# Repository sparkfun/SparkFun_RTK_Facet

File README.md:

SparkFun RTK Facet
========================================

<table class="table table-hover table-striped table-bordered">
  <tr align="center">
   <td></td>
   <td></td>
  <tr align="center">
    <td><a href="https://www.sparkfun.com/products/20000">SparkFun RTK Facet L-Band (GPS-20000)</a></td>
    <td><a href="https://www.sparkfun.com/products/19029">SparkFun RTK Facet (GPS-19029)</a></td>
  </tr>
</table>

The SparkFun RTK Facet and RTK Facet L-Band are your one stop shop for high precision geolocation and surveying needs. For basic users, it’s incredibly easy to get up and running and for advanced users, the RTK Facet is a flexible and powerful tool. With just a few minutes of setup, the RTK Facet is one of the fastest ways to take centimeter grade measurements. By connecting your phone to the RTK Facet over Bluetooth, your phone can act as the radio link to provide correction data as well as receive the NMEA output from the device. This is exactly how $10,000 surveying devices have been operating for the past decade - we just made it easier, smaller, and a lot cheaper. 

The RTK Facet L-Band utilizes corrections from u-blox's PointPerfect service broadcast from a geosynchronous Inmarsat satellite. The only setup required is a WiFi SSID and password. Once entered, the device will provision itself and periodically (once a month) update the decryption keys necessary to use the PointPerfect service. The price of the RTK Facet L-Band includes a 12-month subscription. Additional years of service can be purchased.

Under the hood of the SparkFun RTK Facet is an ESP32 WROOM connected to a ZED-F9P as well as some peripheral hardware (OLED, LiPo fuel gauge, microSD, etc). Additionally, housed under the dome of the RTK Facet is a surveyor grade L1/L2 antenna. It is the same element found within our GNSS Multi-Band L1/L2 Surveying Antenna.

Under the hood of the SparkFun RTK Facet L-Band is an ESP32 WROOM connected to a ZED-F9P GNSS receiver, a NEO-D9S L-Band receiver (for corrections), and a variety of peripheral hardware (LiPo fuel gauge, microSD, etc). Additionally, housed under the dome of the RTK Facet L-Band is a surveyor grade L1/L2/L-Band antenna. This antenna is a unique combination of elements designed to receive the GNSS signals (L1/L2) alongside the 1.55GHz PointPerfect corrections. The built-in antenna has an ARP of 69mm from the base to the measuring point of the L1 antenna and an ARP of 68mm to the measuring point of the L2 antenna. The RTK Facet L-Band is programmed in Arduino and can be tailored by you to fit whatever your needs may be.

Repository Contents
-------------------

* **/Documents** - Datasheets and additional product information
* **/Hardware** - Eagle PCB files
* **/Labels** - Display overlay and info stickers
* **/Mechanical** - Drawings use to created injection molding tooling

Documentation
--------------

* **[RTK Product Manual](https://docs.sparkfun.com/SparkFun_RTK_Firmware/)** - A detailed guide describing all the various software features of the RTK product line. Essentially it is a manual for the firmware used by the RTK Facet.
* **[RTK Facet L-Band Hookup Guide](https://learn.sparkfun.com/tutorials/sparkfun-rtk-facet-l-band-hookup-guide)** - Hookup guide for the SparkFun RTK Facet L-Band.
* **[RTK Facet Hookup Guide](https://learn.sparkfun.com/tutorials/sparkfun-rtk-facet-hookup-guide)** - Hookup guide for the SparkFun RTK Facet.

License Information
-------------------

This product is _**open source**_! 

Please review the LICENSE.md file for license information. 

If you have any questions or concerns on licensing, please contact technical support on our [SparkFun forums](https://forum.sparkfun.com/viewforum.php?f=152).

Distributed as-is; no warranty is given.

- Your friends at SparkFun.

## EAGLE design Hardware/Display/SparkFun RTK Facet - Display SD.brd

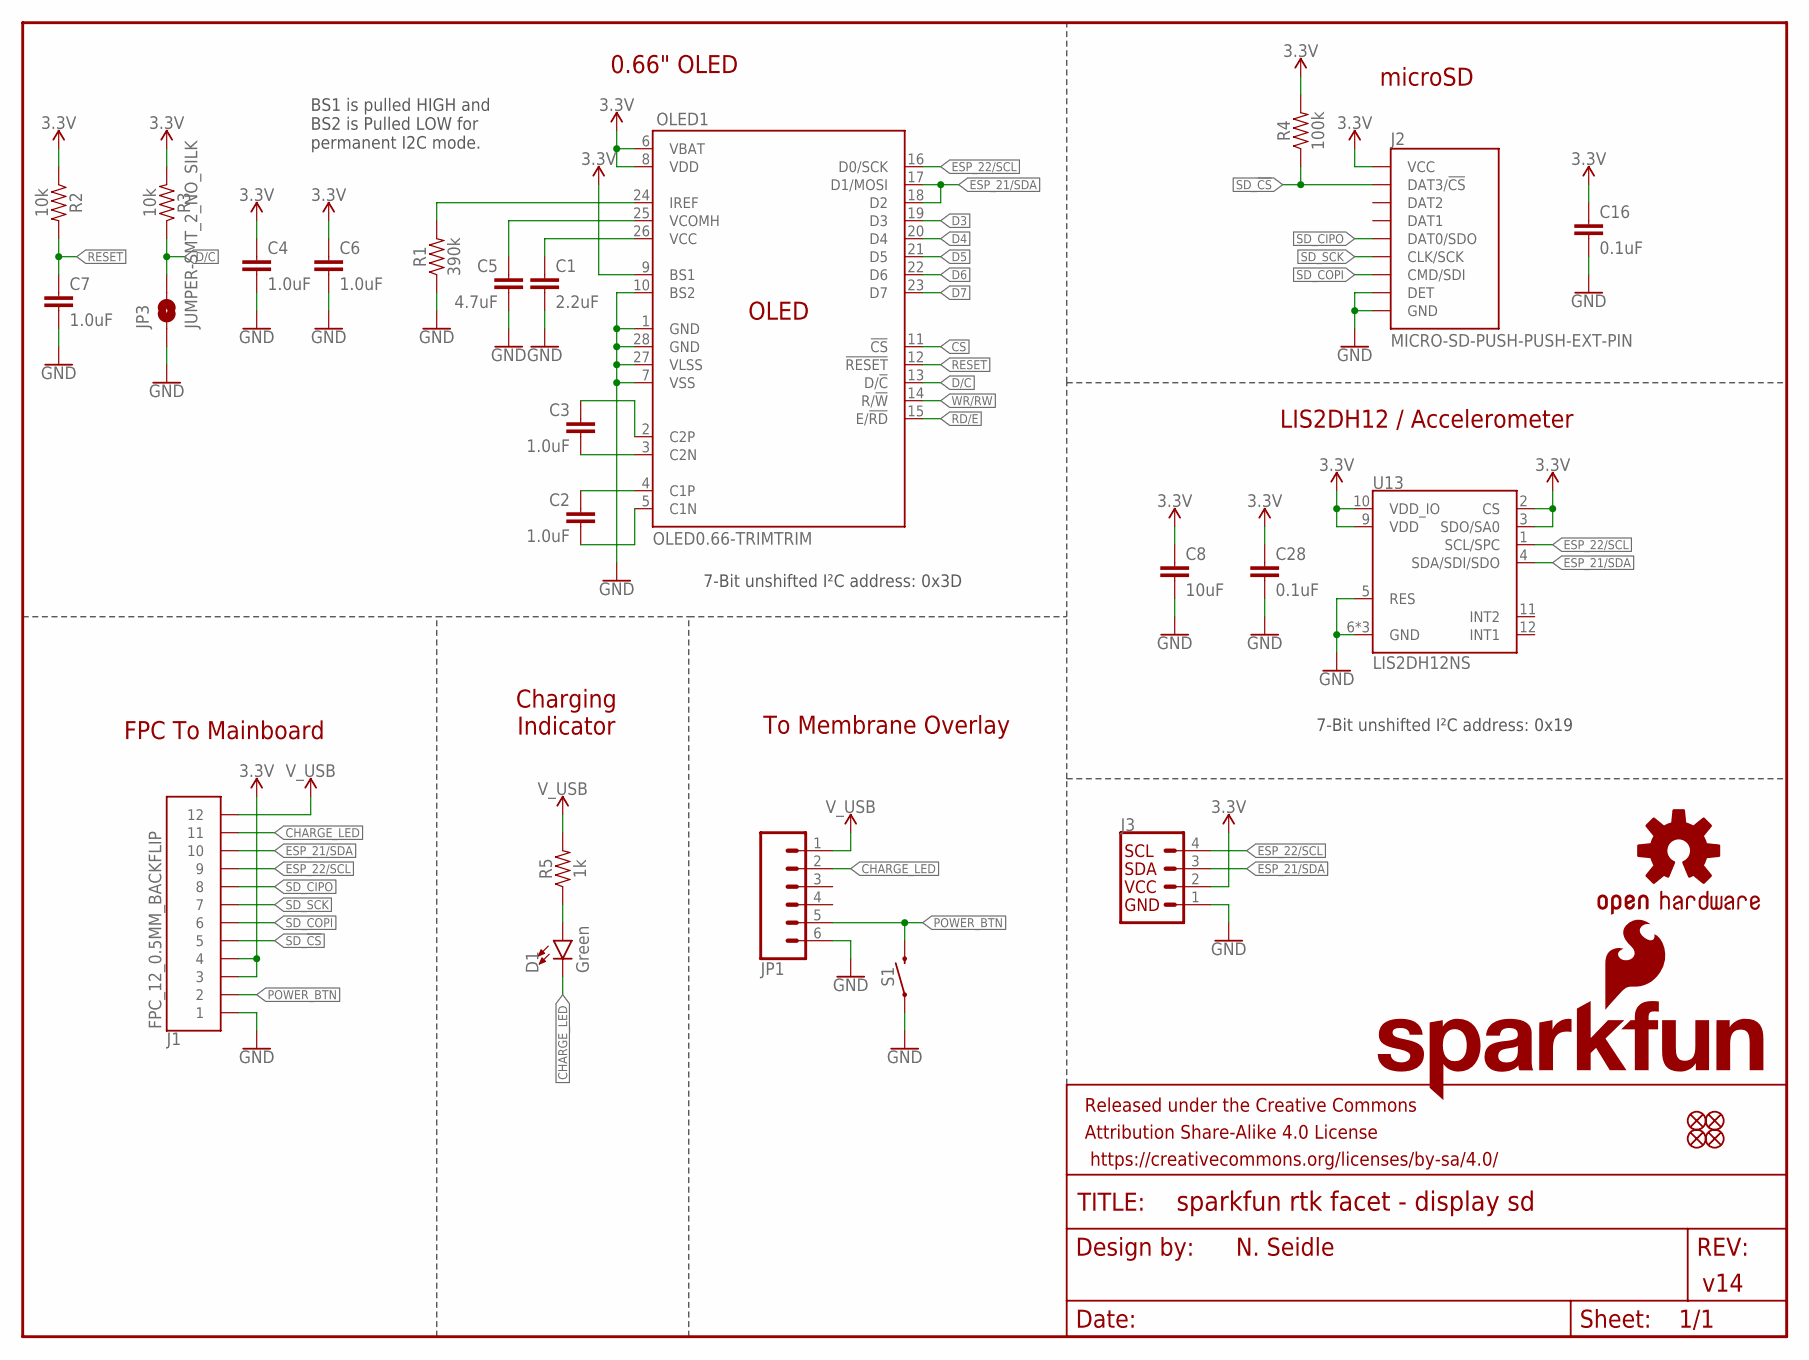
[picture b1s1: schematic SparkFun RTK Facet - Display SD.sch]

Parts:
C1: 2.2uF; 0805
C2, C3: 1.0uF; 0805
C4, C6, C7: 1.0uF; 0603
C5: 4.7uF; 1206
C8: 10uF; 0603
C16, C28: 0.1uF; 0603
D1: Green; LED-1206-BOTTOM
FID1, FID2, FID3, FID4: FIDUCIAL1X2; FIDUCIAL-1X2
FRAME1: FRAME-LETTER; CREATIVE_COMMONS
J1: FPC_12_0.5MM_BACKFLIP; FPC_12_DOUBLESIDED_BACKFLIP
J2: MICRO-SD-PUSH-PUSH-EXT-PIN; MICROSD-EXTERNALPIN
J3: I2C_STANDARD_NO_SILK; 1X04_NO_SILK
JP1: CONN_061MM-LIF; FPC_6_1MM-LIF
JP3: JUMPER-SMT_2_NO_SILK; SMT-JUMPER_2_NO_SILK
LOGO3: OSHW-LOGOMINI; OSHW-LOGO-MINI
LOGO5: SFE_LOGO_NAME_FLAME8_MM; SFE_LOGO_NAME_FLAME_8MM
OLED1: OLED0.66-TRIMTRIM; OLED-0.66-64X48-TRIM
R1: 390k; 0603
R2, R3: 10k; 0603
R4: 100k; 0603
R5: 1k; 0603
S1: MOMENTARY-SWITCH-SPST-SMD-5.2MM-TALL; TACTILE_SWITCH_SMD_5.2MM
U13: LIS2DH12NS; LGA-12-LISDH12-NOSILK

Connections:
3.3V: C4.1, C6.1, C8.1, C16.1, C28.1, J1.3, J1.4, J2.4 (VCC), J3.2, OLED1.6 (VBAT), OLED1.8 (VDD), OLED1.9 (BS1), R2.1, R3.2, R4.2, U13.2 (CS), U13.3 (SDO/SA0), U13.9 (VDD), U13.10 (VDD_IO)
C1P: C2.1, OLED1.4 (C1P)
C2N: C3.2, OLED1.3 (C2N)
CHARGE_LED: D1.C, J1.11, JP1.2
CS: OLED1.11 (!CS!)
D3: OLED1.19 (D3)
D4: OLED1.20 (D4)
D5: OLED1.21 (D5)
D6: OLED1.22 (D6)
D7: OLED1.23 (D7)
D/C: JP3.2, OLED1.13 (D/!C!), R3.1
ESP_21/SDA: J1.10, J3.3, OLED1.17 (D1/MOSI), OLED1.18 (D2), U13.4 (SDA/SDI/SDO)
ESP_22/SCL: J1.9, J3.4, OLED1.16 (D0/SCK), U13.1 (SCL/SPC)
GND: C1.2, C4.2, C5.2, C6.2, C7.2, C8.2, C16.2, C28.2, J1.1, J2.6 (GND), J2.9 (DET), J2.10 (GND), J2.11 (GND), J2.12 (GND), J2.13 (GND), J3.1, JP1.6, JP3.1, OLED1.1 (GND), OLED1.7 (VSS), OLED1.10 (BS2), OLED1.27 (VLSS), OLED1.28 (GND), R1.1, S1.1, U13.5 (RES), U13.6 (GND), U13.7 (GND), U13.8 (GND)
IREF: OLED1.24 (IREF), R1.2
unnamed: C3.1, OLED1.2 (C2P)
unnamed: C2.2, OLED1.5 (C1N)
unnamed: D1.A, R5.1
POWER_BTN: J1.2, JP1.5, S1.3 (2)
RD/E: OLED1.15 (E/!RD!)
RESET: C7.1, OLED1.12 (!RESET!), R2.2
SD_!CS!: J1.5, J2.2 (DAT3/!CS!), R4.1
SD_CIPO: J1.8, J2.7 (DAT0/SDO)
SD_COPI: J1.6, J2.3 (CMD/SDI)
SD_SCK: J1.7, J2.5 (CLK/SCK)
VCC: C1.1, OLED1.26 (VCC)
VCOMH: C5.1, OLED1.25 (VCOMH)
V_USB: J1.12, JP1.1, R5.2
WR/RW: OLED1.14 (R/!W!)

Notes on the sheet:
v14
FPC To Mainboard
BS1 is pulled HIGH and BS2 is Pulled LOW for permanent I2C mode.
microSD
7-Bit unshifted I²C address: 0x19
LIS2DH12 / Accelerometer
To Membrane Overlay
0.66" OLED
Charging Indicator
N. Seidle
7-Bit unshifted I²C address: 0x3D

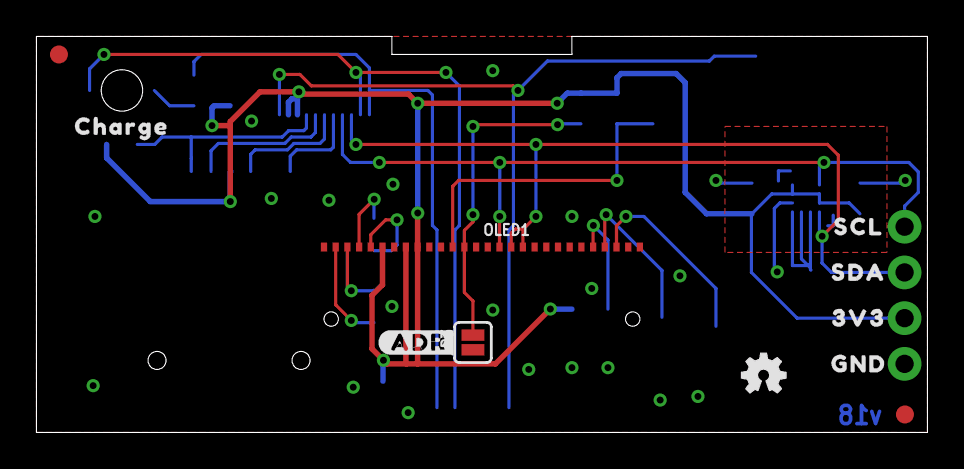
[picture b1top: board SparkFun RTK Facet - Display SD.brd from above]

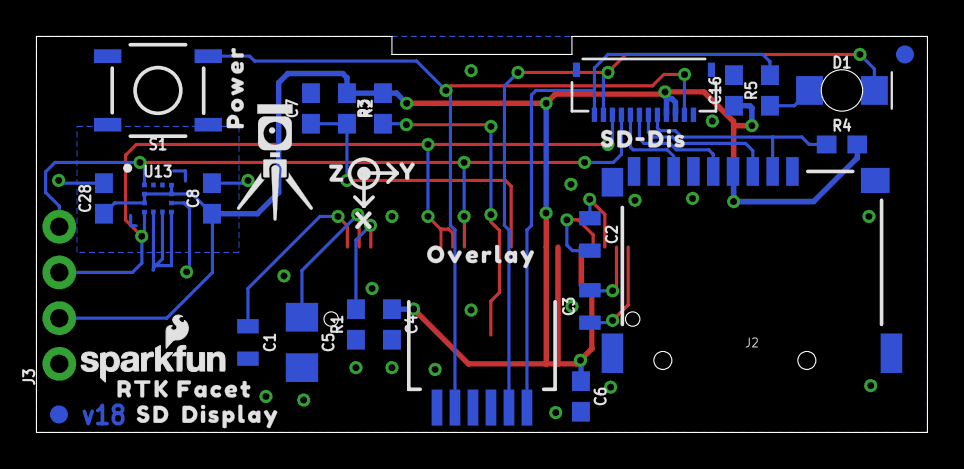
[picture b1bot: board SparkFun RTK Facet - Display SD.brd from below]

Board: 2 copper layers, 49.5 x 22.0 mm, 48 parts (37 on the bottom side), 21 nets.

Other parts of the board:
U$1: SD#DIS0
U$2: OVERLAY0
U$3: DISPLAY0
U$4: SD1
U$5: RTK5#SVG0
U$6: SPECIAL_INSTRUCTIONS-ORDERING; ORDERING_INSTRUCTIONS
U$7: #ADR#0
U$8: CHARGE0
U$9: POWER0
U$10: X0
U$11: Y1
U$12: Z2
U$13: RTK_FACET0
U$14: 3V33
U$15: GND2
U$16: SCL0
U$17: SDA1

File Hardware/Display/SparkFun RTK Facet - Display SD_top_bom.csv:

Comment,Designator,Footprint,LCSC Part #
OLED0.66-TRIMTRIM,OLED1,OLED-0.66-64X48-TRIM,C88334 
0.1uF,C16 C28,603,C1590 
1.0uF,C2 C3,805,C15849 
1.0uF,C4 C6 C7,603,C1592 
1k,R5,603,C22548 
2.2uF,C1,805,C19110 
4.7uF,C5,1206,C51205 
10k,R2 R3,603,C98220 
10uF,C8,603,C19702 
100k,R4,603,C14675 
390k,R1,603,C863775 
FPC_12_0.5MM_BACKFLIP,J1,FPC_12_DOUBLESIDED_BACKFLIP,C5213751 
Green,D1,LED-1206-BOTTOM,C125106 
MICRO-SD-PUSH-PUSH-EXT-PIN,J2,MICROSD-EXTERNALPIN,C720505 
MOMENTARY-SWITCH-SPST-SMD-5.2MM-TALL,S1,TACTILE_SWITCH_SMD_5.2MM,C318887 
6P_1MM-LIF Connector,JP1,6P_1MM-LIF Connector,C2915488

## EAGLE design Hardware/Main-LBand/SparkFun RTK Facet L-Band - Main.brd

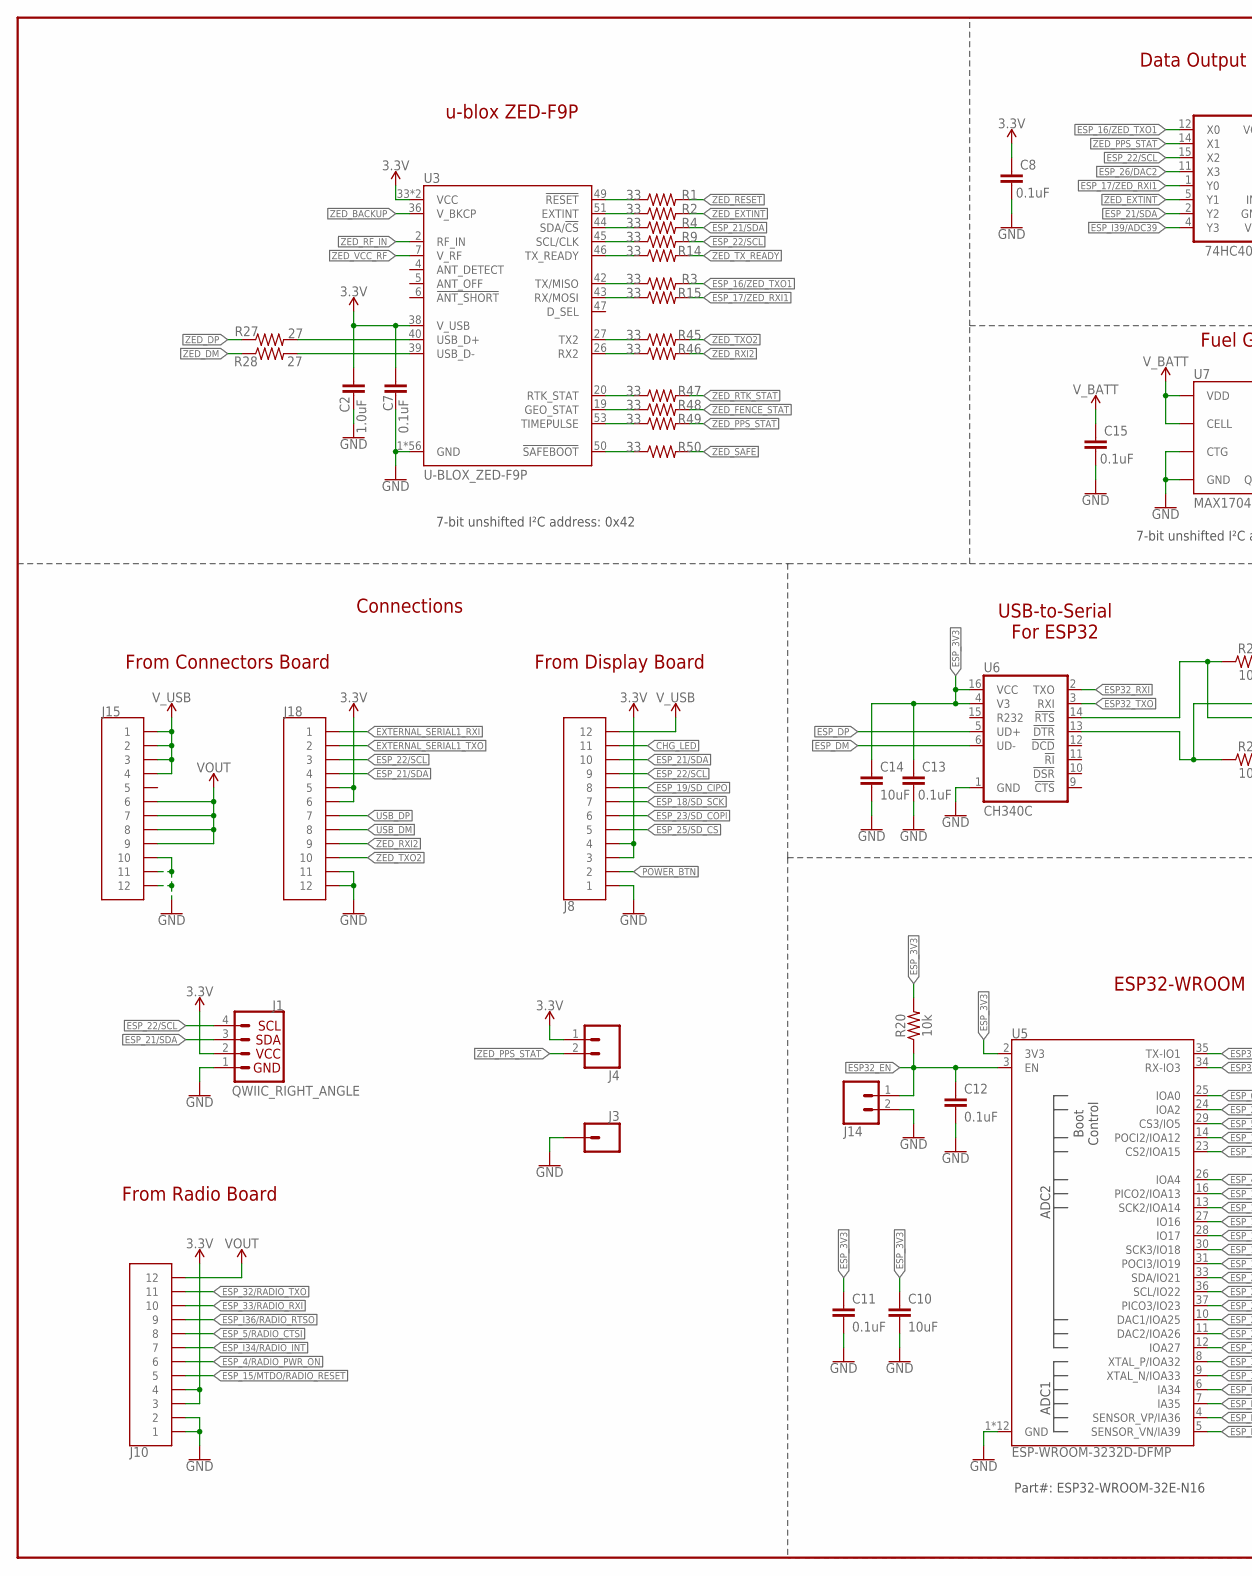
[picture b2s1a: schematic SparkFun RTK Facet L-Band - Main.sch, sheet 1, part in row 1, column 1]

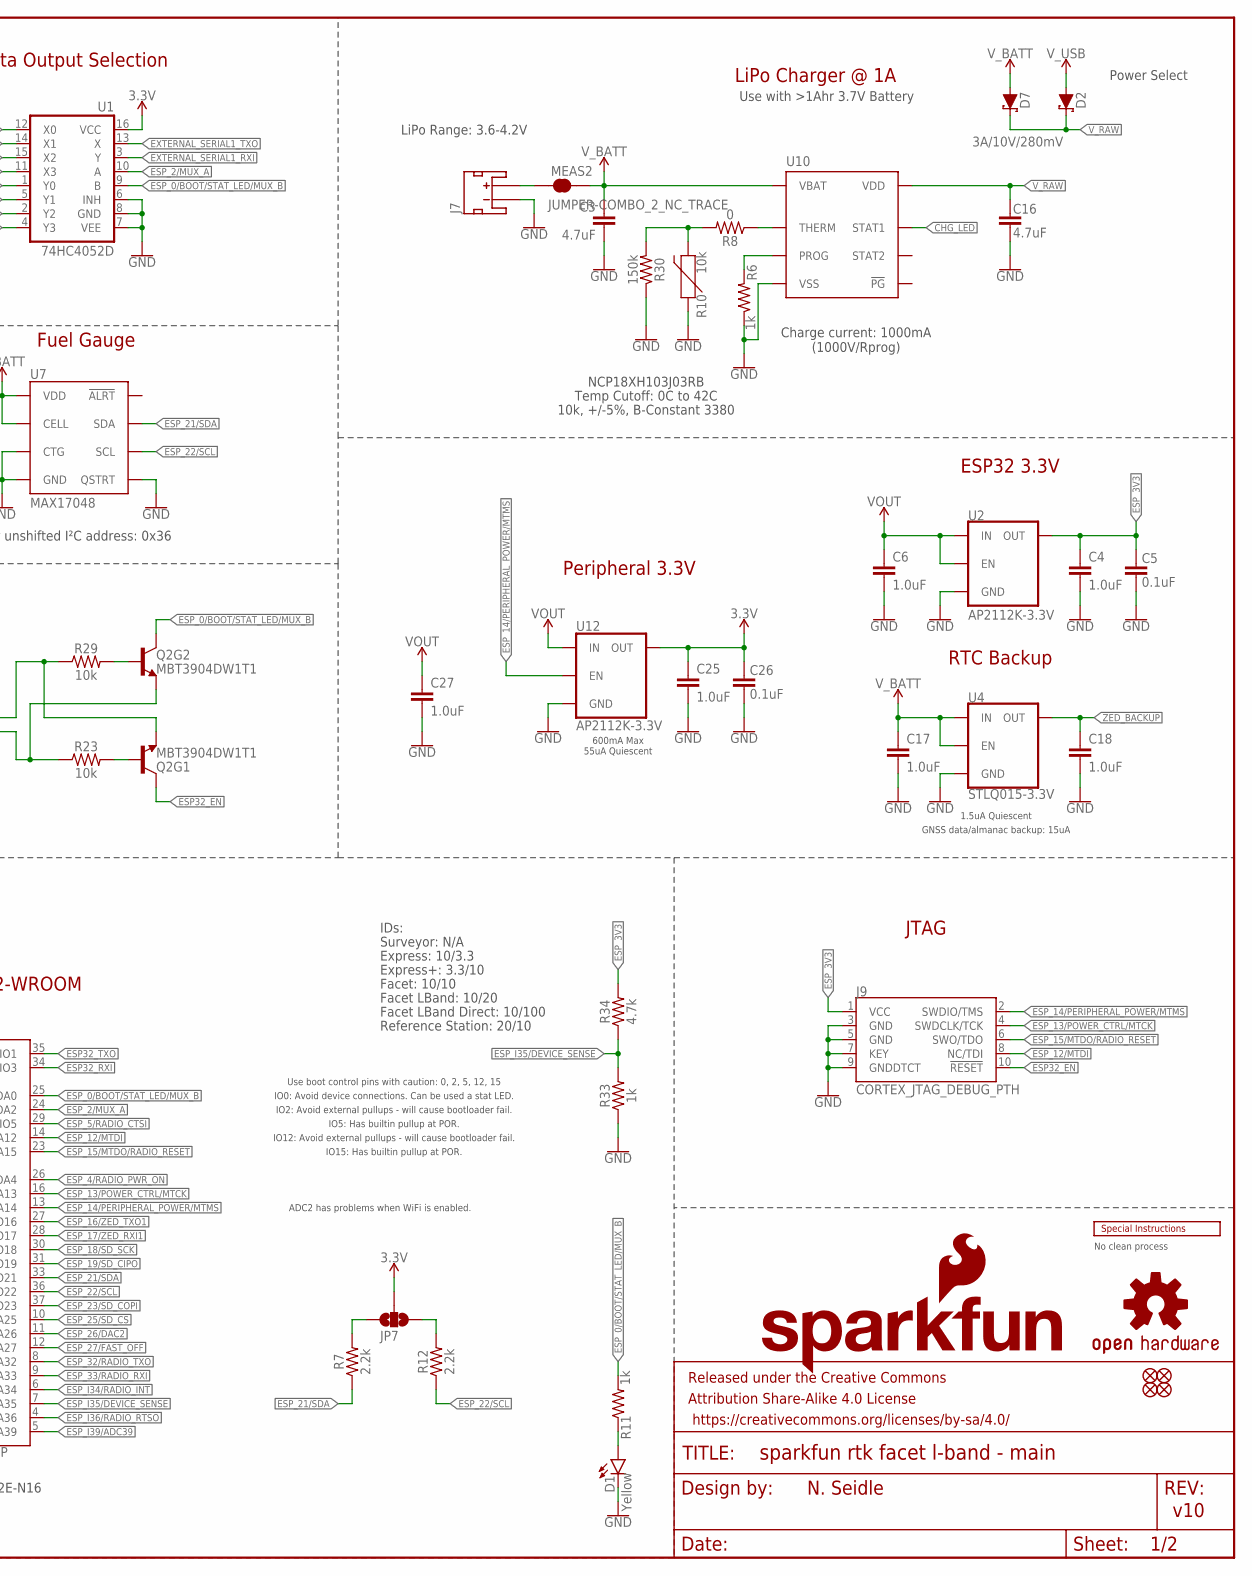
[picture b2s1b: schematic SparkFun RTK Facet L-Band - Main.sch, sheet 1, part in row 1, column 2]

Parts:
C2, C4, C6, C17, C18, C25, C27: 1.0uF; 0603
C3, C16: 4.7uF; 0603
C5, C7, C8, C11, C12, C13, C15, C26: 0.1uF; 0603
C10, C14: 10uF; 0603
D1: Yellow; LED-0603
D2, D7: 3A/10V/280mV; SOD-323
FRAME2: FRAME-LEDGER; CREATIVE_COMMONS
J1: QWIIC_RIGHT_ANGLE; JST04_1MM_RA
J3: CONN_01PTH_NO_SILK_YES_STOP; 1X01_NO_SILK
J4, J14: CONN_021X02_NO_SILK; 1X02_NO_SILK
J7: JST_2MM_MALE; JST-2-SMD
J8, J10, J15, J18: FPC_12_0.5MM_BACKFLIP; FPC_12_DOUBLESIDED_BACKFLIP
J9: CORTEX_JTAG_DEBUG_PTH; 2X5-PTH-1.27MM
JP7: JUMPER-SMT_3_NO_SILK; SMT-JUMPER_3_NO_SILK
JP21, JP61, JP71, JP81: FIDUCIALUFIDUCIAL; FIDUCIAL-MICRO
LOGO1: OSHW-LOGOMINI; OSHW-LOGO-MINI
LOGO2: SFE_LOGO_NAME_FLAME.1_INCH; SFE_LOGO_NAME_FLAME_.1
MEAS2: JUMPER-COMBO_2_NC_TRACE; COMBO-JUMPER_2_NC_TRACE
Q2: MBT3904DW1T1; SC70-6
R1, R2, R3, R4, R9, R14, R15, R45, R46, R47, R48, R49, R50: 33; 0603
R6, R11, R33: 1k; 0603
R7, R12: 2.2k; 0603
R8: 0; 0603
R10, R20, R23, R29: 10k; 0603
R27, R28: 27; 0603
R30: 150k; 0603
R34: 4.7k; 0603
U1: 74HC4052D; SO16
U2, U12: AP2112K-3.3V; SOT23-5
U3: U-BLOX_ZED-F9P; ZED-F9P
U4: STLQ015-3.3V; SOT23-5
U5: ESP-WROOM-3232D-DFMP; ESP-WROOM-32D-DFM_PASTE
U6: CH340C; SO016
U7: MAX17048; DFN-8
U10: MCP73833MSOP; MSOP10
U$2: SPECIAL_INSTRUCTIONS-ORDERING; ORDERING_INSTRUCTIONS

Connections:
3.3V: C2.1, C7.2, C8.1, C25.1, C26.2, J1.2, J4.1, J8.3, J8.4, J10.3, J10.4, J18.5, J18.6, JP7.2, U1.16 (VCC), U3.33 (VCC), U3.34 (VCC), U3.38 (V_USB), U12.5 (OUT); also elsewhere on the board
CHG_LED: J8.11, U10.3 (STAT1)
CHG_THERM1: R8.2, R10.2, R30.2
ESP32_!DTR: Q2.1 (E), R23.1, U6.13 (!DTR)
ESP32_!RTS: Q2.4 (E), R29.1, U6.14 (!RTS)
ESP32_EN: C12.1, J9.10 (!RESET), J14.1, Q2.3 (C), R20.1, U5.3 (EN)
ESP32_RXI: U5.34 (RX-IO3), U6.2 (TXO)
ESP32_TXO: U5.35 (TX-IO1), U6.3 (RXI)
ESP_0/BOOT/STAT_LED/MUX_B: Q2.6 (C), R11.2, U1.9 (B), U5.25 (IOA0)
ESP_2/MUX_A: U1.10 (A), U5.24 (IOA2)
ESP_3V3: C4.1, C5.2, C10.1, C11.1, C13.1, C14.1, J9.1 (VCC), R20.2, R34.2, U2.5 (OUT), U5.2 (3V3), U6.4 (V3), U6.16 (VCC); also elsewhere on the board
ESP_4/RADIO_PWR_ON: J10.6, U5.26 (IOA4)
ESP_5/RADIO_CTSI: J10.8, U5.29 (CS3/IO5)
ESP_12/MTDI: J9.8 (NC/TDI), U5.14 (POCI2/IOA12)
ESP_13/POWER_CTRL/MTCK: J9.4 (SWDCLK/TCK), U5.16 (PICO2/IOA13); also elsewhere on the board
ESP_14/PERIPHERAL_POWER/MTMS: J9.2 (SWDIO/TMS), U5.13 (SCK2/IOA14), U12.3 (EN)
ESP_15/MTDO/RADIO_!RESET!: J9.6 (SWO/TDO), J10.5, U5.23 (CS2/IOA15)
ESP_16/ZED_TXO1: R3.2, U1.12 (X0), U5.27 (IO16)
ESP_17/ZED_RXI1: R15.2, U1.1 (Y0), U5.28 (IO17)
ESP_18/SD_SCK: J8.7, U5.30 (SCK3/IO18)
ESP_19/SD_CIPO: J8.8, U5.31 (POCI3/IO19)
ESP_21/SDA: J1.3, J8.10, J18.4, R4.2, R7.1, U1.2 (Y2), U5.33 (SDA/IO21), U7.8 (SDA); also elsewhere on the board
ESP_22/SCL: J1.4, J8.9, J18.3, R9.2, R12.1, U1.15 (X2), U5.36 (SCL/IO22), U7.7 (SCL); also elsewhere on the board
ESP_23/SD_COPI: J8.6, U5.37 (PICO3/IO23)
ESP_25/SD_!CS!: J8.5, U5.10 (DAC1/IOA25)
ESP_26/DAC2: U1.11 (X3), U5.11 (DAC2/IOA26)
ESP_27/FAST_OFF: U5.12 (IOA27); also elsewhere on the board
ESP_32/RADIO_TXO: J10.11, U5.8 (XTAL_P/IOA32)
ESP_33/RADIO_RXI: J10.10, U5.9 (XTAL_N/IOA33)
ESP_DM: U6.6 (UD-); also elsewhere on the board
ESP_DP: U6.5 (UD+); also elsewhere on the board
ESP_I34/RADIO_INT: J10.7, U5.6 (IA34)
ESP_I35/DEVICE_SENSE: R33.2, R34.1, U5.7 (IA35)
ESP_I36/RADIO_RTSO: J10.9, U5.4 (SENSOR_VP/IA36)
ESP_I39/ADC39: U1.4 (Y3), U5.5 (SENSOR_VN/IA39)
EXTERNAL_SERIAL1_RXI: J18.1, U1.3 (Y)
EXTERNAL_SERIAL1_TXO: J18.2, U1.13 (X)
FENCE_LV: R48.1, U3.19 (GEO_STAT)
GND: C2.2, C3.2, C4.2, C5.1, C6.2, C7.1, C8.2, C10.2, C11.2, C12.2, C13.2, C14.2, C15.2, C16.2, C17.2, C18.2, C25.2, C26.1, C27.2, D1.C, J1.1, J3.1, J7.1 (-), J8.1, J9.3 (GND), J9.5 (GND), J9.7 (KEY), J9.9 (GNDDTCT), J10.1, J10.2, J14.2, J15.10, J15.11, J15.12, J18.11, J18.12, R6.1, R10.1, R30.1, R33.1, U1.6 (INH), U1.7 (VEE), U1.8 (GND), U2.2 (GND), U3.1 (GND), U3.3 (GND), U3.12 (GND), U3.14 (GND), U3.32 (GND), U3.37 (GND), U3.41 (GND), U3.48 (GND), U3.55 (GND), U3.56 (GND), U3.57 (GND), U3.58 (GND), U3.59 (GND), U3.60 (GND), U3.61 (GND), U3.62 (GND), U3.63 (GND), U3.64 (GND), U3.65 (GND), U3.66 (GND), U3.67 (GND), U3.68 (GND), U3.69 (GND), U3.70 (GND), U3.71 (GND), U3.72 (GND), U3.73 (GND), U3.74 (GND), U3.75 (GND), U3.76 (GND), U3.77 (GND), U3.78 (GND), U3.79 (GND), U3.80 (GND), U3.81 (GND), U3.82 (GND), U3.83 (GND), U3.84 (GND), U3.85 (GND), U3.86 (GND), U3.87 (GND), U3.88 (GND), U3.89 (GND), U3.90 (GND), U3.91 (GND), U3.92 (GND), U3.93 (GND), U3.94 (GND), U3.95 (GND), U3.96 (GND), U3.97 (GND), U3.98 (GND), U3.99 (GND), U3.100 (GND), U3.101 (GND), U3.102 (GND), U4.2 (GND), U5.1 (GND), U5.15 (GND), U5.38 (GND), U5.GND, U5.GNDT1 (GND), U5.GNDT2 (GND), U5.GNDT3 (GND), U5.GNDT4 (GND), U5.GNDT5 (GND), U5.GNDT6 (GND), U5.GNDT7 (GND), U5.GNDT8 (GND), U6.1 (GND), U7.1 (CTG), U7.4 (GND), U7.6 (QSTRT), U7.9 (GND), U10.5 (VSS), U12.2 (GND); also elsewhere on the board
LIPO_RAW: J7.2 (+), MEAS2.1, MEAS2.3 (1)
unnamed: R8.1, U10.8 (THERM)
unnamed: D1.A, R11.1
unnamed: JP7.3, R7.2
unnamed: JP7.1, R12.2
unnamed: R2.1, U3.51 (EXTINT)
unnamed: R27.2, U3.40 (USB_D+)
unnamed: R28.2, U3.39 (USB_D-)
unnamed: R1.1, U3.49 (!RESET!)
unnamed: R50.1, U3.50 (!SAFEBOOT!)
unnamed: R14.1, U3.46 (TX_READY)
unnamed: Q2.5 (B), R23.2
unnamed: Q2.2 (B), R29.2
POWER_BTN: J8.2; also elsewhere on the board
PPS: R49.1, U3.53 (TIMEPULSE)
PROG1: R6.2, U10.6 (PROG)
RTK_LV: R47.1, U3.20 (RTK_STAT)
RX2_LV: R46.1, U3.26 (RX2)
RXLV: R15.1, U3.43 (RX/MOSI)
SCL_LV: R9.1, U3.45 (SCL/CLK)
SDA_LV: R4.1, U3.44 (SDA/!CS!)
TX2_LV: R45.1, U3.27 (TX2)
TXLV: R3.1, U3.42 (TX/MISO)
USB_DM: J18.8; also elsewhere on the board
USB_DP: J18.7; also elsewhere on the board
VOUT: C6.1, C27.1, J10.12, J15.6, J15.7, J15.8, J15.9, U2.1 (IN), U2.3 (EN), U12.1 (IN); also elsewhere on the board
V_BATT: C3.1, C15.1, C17.1, D7.A, MEAS2.2, MEAS2.4 (2), U4.1 (IN), U4.3 (EN), U7.2 (CELL), U7.3 (VDD), U10.9 (VBAT), U10.10 (VBAT)
V_RAW: C16.1, D2.C, D7.C, U10.1 (VDD), U10.2 (VDD); also elsewhere on the board
V_USB: D2.A, J8.12, J15.1, J15.2, J15.3, J15.4; also elsewhere on the board
ZED_!RESET!: R1.2
ZED_!SAFE!: R50.2
ZED_BACKUP: C18.1, U3.36 (V_BKCP), U4.5 (OUT)
ZED_DM: R28.1; also elsewhere on the board
ZED_DP: R27.1; also elsewhere on the board
ZED_EXTINT: R2.2, U1.5 (Y1)
ZED_FENCE_STAT: R48.2
ZED_PPS_STAT: J4.2, R49.2, U1.14 (X1)
ZED_RF_IN: U3.2 (RF_IN); also elsewhere on the board
ZED_RTK_STAT: R47.2
ZED_RXI2: J18.9, R46.2; also elsewhere on the board
ZED_TXO2: J18.10, R45.2; also elsewhere on the board
ZED_TX_READY: R14.2
ZED_VCC_RF: U3.7 (V_RF); also elsewhere on the board

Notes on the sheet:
v10
7-bit unshifted I²C address: 0x42
u-blox ZED-F9P
RTC Backup
No clean process
Connections
ESP32 3.3V
ESP32-WROOM
USB-to-Serial For ESP32
Data Output Selection
Fuel Gauge
From Connectors Board
From Display Board
LiPo Range: 3.6-4.2V
Charge current: 1000mA (1000V/Rprog)
Use with >1Ahr 3.7V Battery
LiPo Charger @ 1A
NCP18XH103J03RB
10k, +/-5%, B-Constant 3380
Temp Cutoff: 0C to 42C
Power Select
1.5uA Quiescent
GNSS data/almanac backup: 15uA
Peripheral 3.3V
600mA Max 55uA Quiescent
IO0: Avoid device connections. Can be used a stat LED.
ADC2 has problems when WiFi is enabled.
IO12: Avoid external pullups - will cause bootloader fail.
Use boot control pins with caution: 0, 2, 5, 12, 15
IO2: Avoid external pullups - will cause bootloader fail.
IO15: Has builtin pullup at POR.
IO5: Has builtin pullup at POR.
From Radio Board
N. Seidle
JTAG
Part#: ESP32-WROOM-32E-N16
IDs:
Surveyor: N/A
Express: 10/3.3
Express+: 3.3/10

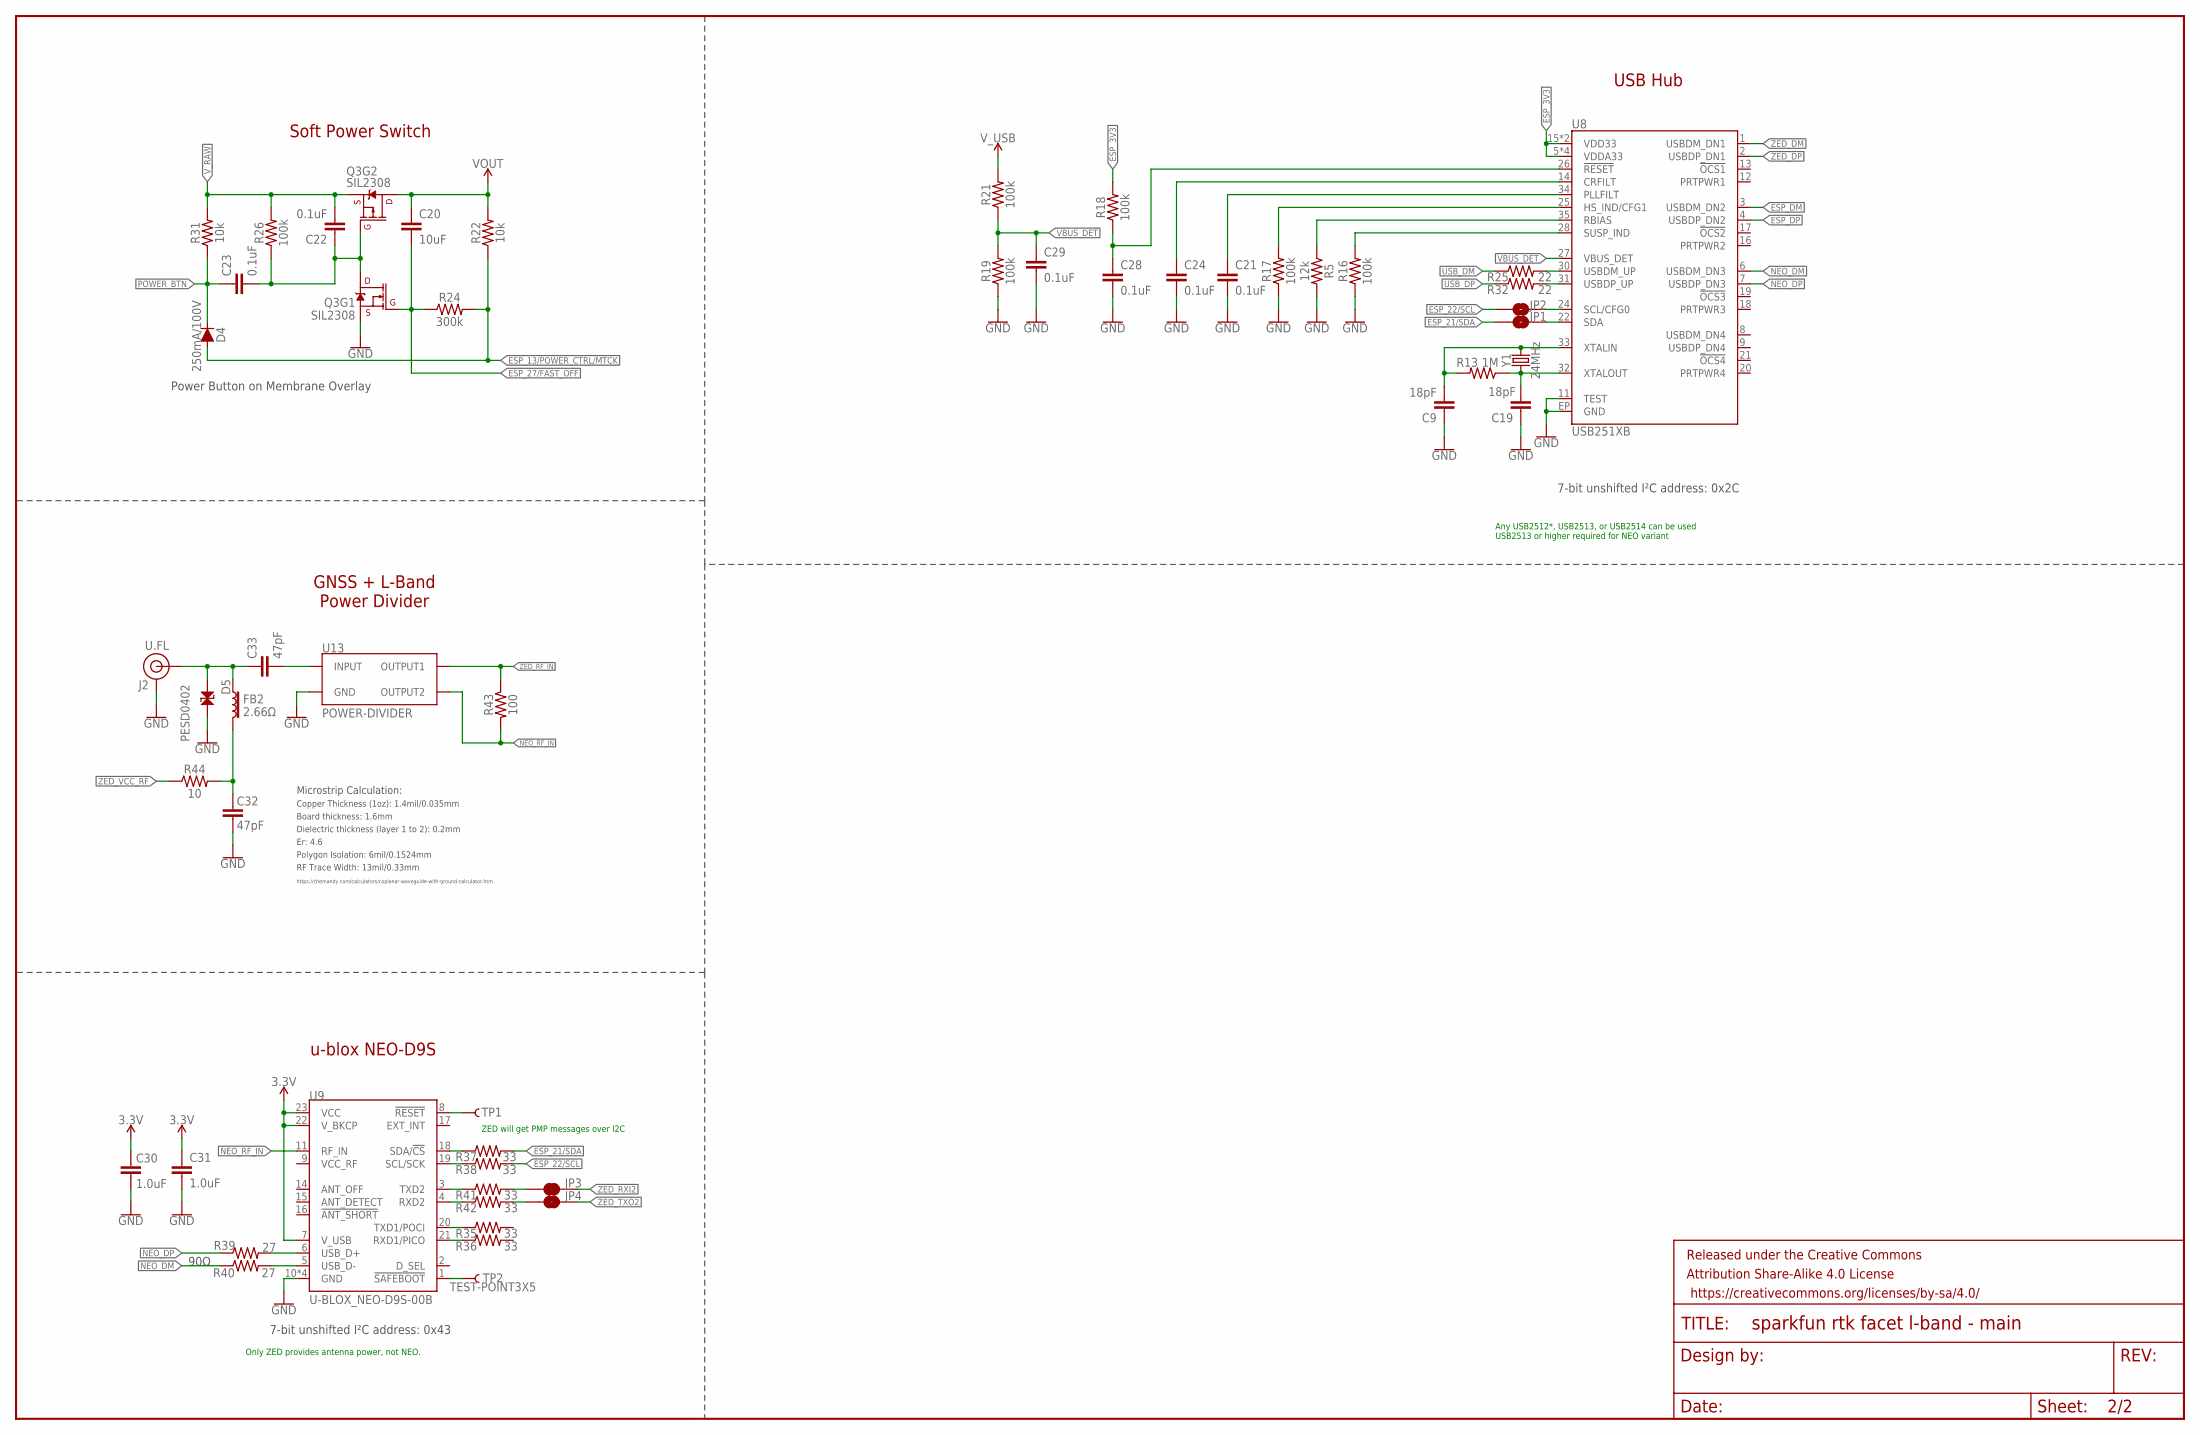
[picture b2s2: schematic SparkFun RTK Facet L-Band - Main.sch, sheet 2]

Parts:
C9, C19: 18pF; 0603
C20: 10uF; 0603
C21, C22, C23, C24, C28, C29: 0.1uF; 0603
C30, C31: 1.0uF; 0603
C32, C33: 47pF; 0402-TIGHT
D4: 250mA/100V; SOD-323
D5: PESD0402; 0402-TIGHT
FB2: 2.66Ω; 0402-TIGHT
FRAME1: FRAME-LEDGER; CREATIVE_COMMONS
J2: U.FL
JP1, JP2: JUMPER-SMT_2_NO_SILK; SMT-JUMPER_2_NO_SILK
JP3, JP4: JUMPER-SMT_2_NC_TRACE_SILK; SMT-JUMPER_2_NC_TRACE_SILK
Q3: SIL2308; SOT26
R5: 12k; 0603
R13: 1M; 0603
R16, R17, R18, R19, R21, R26: 100k; 0603
R22, R31: 10k; 0603
R24: 300k; 0603
R25, R32: 22; 0603
R35, R36, R37, R38, R41, R42: 33; 0603
R39, R40: 27; 0603
R43: 100; 0603
R44: 10; 0402-TIGHT
TP1, TP2: TEST-POINT3X5; PAD.03X.05
U8: USB251XB; QFN-36
U9: U-BLOX_NEO-D9S-00B; NEO-M9N/M8T/M8U/D9S/F9P
U13: POWER-DIVIDER; PD0922J5050S2HF_ANA
Y1: 24MHz; CRYSTAL-SMD-2.0X1.6MM

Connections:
3.3V: C30.1, C31.1, U9.7 (V_USB), U9.22 (V_BKCP), U9.23 (VCC); also elsewhere on the board
ESP_3V3: R18.2, U8.5 (VDDA33), U8.10 (VDDA33), U8.15 (VDD33), U8.23 (VDD33), U8.29 (VDDA33), U8.36 (VDDA33); also elsewhere on the board
ESP_13/POWER_CTRL/MTCK: D4.A, R22.1, R24.2; also elsewhere on the board
ESP_21/SDA: JP1.1, R37.2; also elsewhere on the board
ESP_22/SCL: JP2.1, R38.2; also elsewhere on the board
ESP_27/FAST_OFF: C20.2, Q3.G1 (G), R24.1; also elsewhere on the board
ESP_DM: U8.3 (USBDM_DN2); also elsewhere on the board
ESP_DP: U8.4 (USBDP_DN2); also elsewhere on the board
GND: C9.1, C19.1, C21.2, C24.2, C28.2, C29.2, C30.2, C31.2, C32.2, D5.2, J2.1 (GND), J2.2 (GND), Q3.S1 (S), R5.2, R16.1, R17.1, R19.1, U8.11 (TEST), U8.EP (GND), U9.10 (GND), U9.12 (GND), U9.13 (GND), U9.24 (GND), U13.1 (GND), U13.3 (GND), U13.5 (GND); also elsewhere on the board
unnamed: C22.1, C23.2, Q3.D1 (D), Q3.G2 (G), R26.1
unnamed: C9.2, R13.2, U8.33 (XTALIN), Y1.3 (2)
unnamed: C19.2, R13.1, U8.32 (XTALOUT), Y1.1
unnamed: R5.1, U8.35 (RBIAS)
unnamed: R16.2, U8.28 (SUSP_IND)
unnamed: JP3.1, R41.2
unnamed: R17.2, U8.25 (HS_IND/CFG1)
unnamed: C21.1, U8.34 (PLLFILT)
unnamed: C24.1, U8.14 (CRFILT)
unnamed: R25.2, U8.30 (USBDM_UP)
unnamed: R32.2, U8.31 (USBDP_UP)
unnamed: JP1.2, U8.22 (SDA)
unnamed: JP2.2, U8.24 (SCL/CFG0)
unnamed: R39.2, U9.6 (USB_D+)
unnamed: R40.2, U9.5 (USB_D-)
unnamed: R41.1, U9.3 (TXD2)
unnamed: R42.1, U9.4 (RXD2)
unnamed: R35.1, U9.20 (TXD1/POCI)
unnamed: R36.1, U9.21 (RXD1/PICO)
unnamed: R37.1, U9.18 (SDA/!CS!)
unnamed: R38.1, U9.19 (SCL/SCK)
unnamed: C32.1, FB2.2, R44.2
unnamed: JP4.1, R42.2
unnamed: C33.2, U13.2 (INPUT)
NEO_!RESET!: TP1.1, U9.8 (!RESET!)
NEO_!SAFEBOOT!: TP2.1, U9.1 (!SAFEBOOT!)
NEO_DM: R40.1, U8.6 (USBDM_DN3)
NEO_DP: R39.1, U8.7 (USBDP_DN3)
NEO_RF_IN: R43.2, U9.11 (RF_IN), U13.6 (OUTPUT2)
POWER_BTN: C23.1, D4.C, R31.1; also elsewhere on the board
RF_IN: C33.1, D5.1, FB2.1, J2.FEED (SIGNAL)
USB_!RESET: C28.1, R18.1, U8.26 (!RESET)
USB_DM: R25.1; also elsewhere on the board
USB_DP: R32.1; also elsewhere on the board
VBUS_DET: C29.1, R19.2, R21.1, U8.27 (VBUS_DET)
VOUT: C20.1, Q3.D2 (D), R22.2; also elsewhere on the board
V_RAW: C22.2, Q3.S2 (S), R26.2, R31.2; also elsewhere on the board
V_USB: R21.2; also elsewhere on the board
ZED_DM: U8.1 (USBDM_DN1); also elsewhere on the board
ZED_DP: U8.2 (USBDP_DN1); also elsewhere on the board
ZED_RF_IN: R43.1, U13.4 (OUTPUT1); also elsewhere on the board
ZED_RXI2: JP3.2; also elsewhere on the board
ZED_TXO2: JP4.2; also elsewhere on the board
ZED_VCC_RF: R44.1; also elsewhere on the board

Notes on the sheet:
Soft Power Switch
7-bit unshifted I²C address: 0x2C
USB Hub
Power Button on Membrane Overlay
Any USB2512*, USB2513, or USB2514 can be used USB2513 or higher required for NEO variant
7-bit unshifted I²C address: 0x43
u-blox NEO-D9S
90Ω
Only ZED provides antenna power, not NEO.
ZED will get PMP messages over I2C
GNSS + L-Band Power Divider
Board thickness: 1.6mm
Er: 4.6
Copper Thickness (1oz): 1.4mil/0.035mm
RF Trace Width: 13mil/0.33mm
Polygon Isolation: 6mil/0.1524mm
Dielectric thickness (layer 1 to 2): 0.2mm
https://chemandy.com/calculators/coplanar-waveguide-with-ground-calculator.htm
Microstrip Calculation:

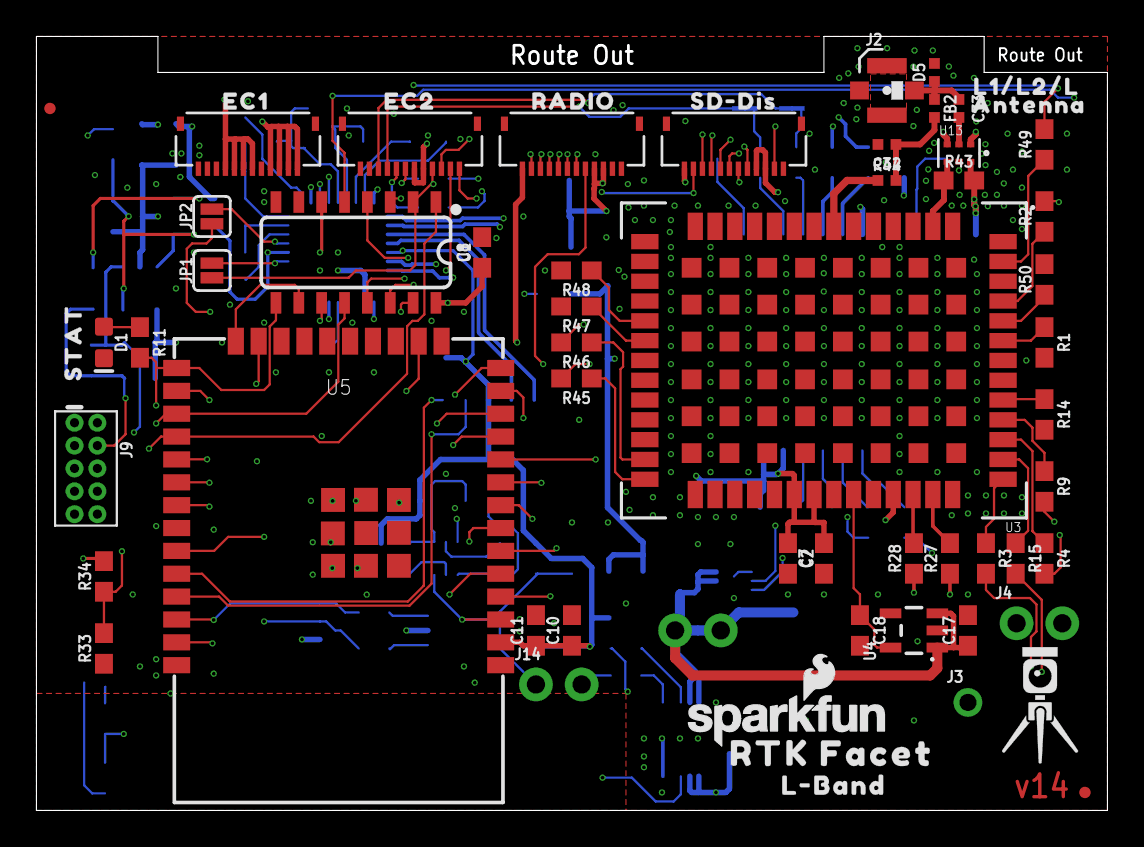
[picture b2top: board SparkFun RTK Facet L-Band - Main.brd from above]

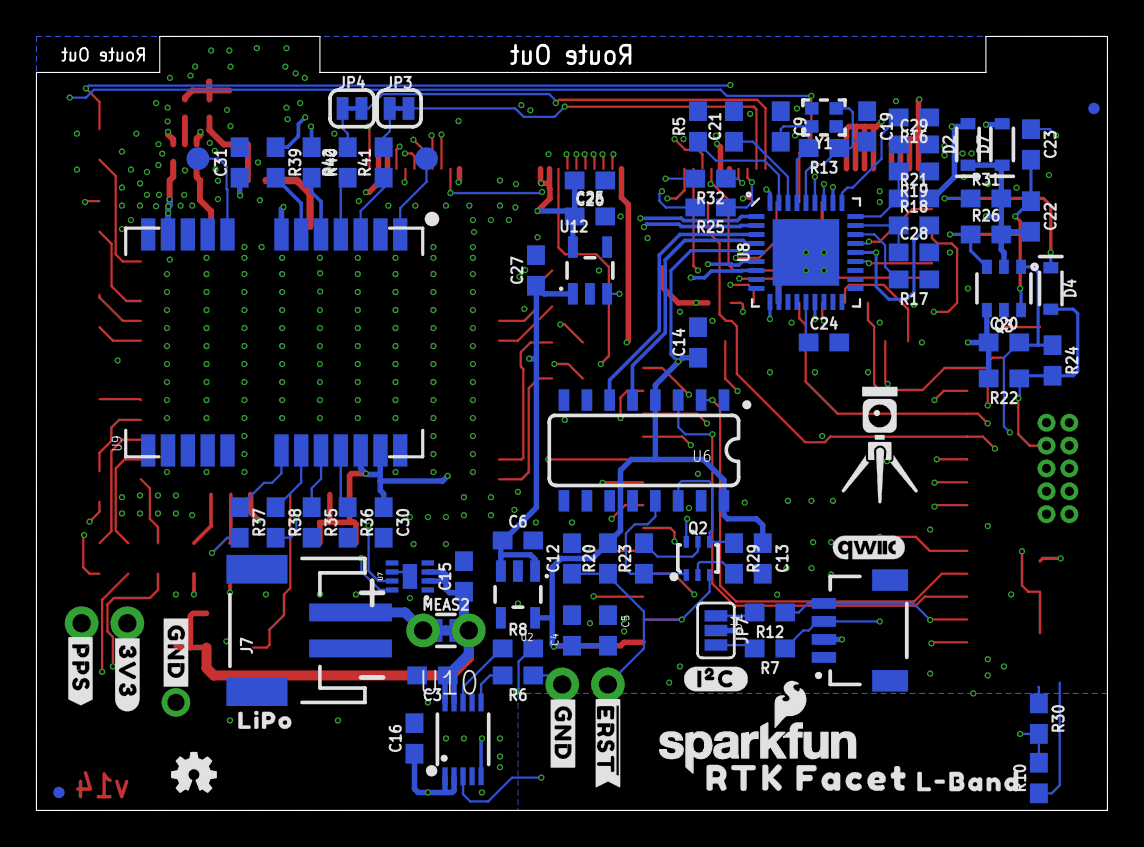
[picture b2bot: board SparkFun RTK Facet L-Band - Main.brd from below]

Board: 4 copper layers, 59.5 x 43.0 mm, 153 parts (89 on the bottom side), 109 nets.

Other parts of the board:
LOGO3: SFE_LOGO_NAME_FLAME.1_INCH; SFE_LOGO_NAME_FLAME_.1
U$1: LIPO0
U$3: EC21
U$4: SD#DIS0
U$5, U$7: L#BAND0
U$6: #3V3#0
U$8: EC10
U$10: #PPS#1
U$11, U$13: RTK_FACET0
U$12: RADIO0
U$14, U$84: #GND#1
U$15, U$16: RTK5#SVG0
U$17: ANTENNA1
U$18: L1#L2#L0
U$24: STAT0
U$25: #I�C#0
U$26: ##ERST##0
U$30: QWIIC_4MM

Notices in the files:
parts and their libraries:
SparkFun-Aesthetics: Licensing: Creative Commons ShareAlike 4.0 International - https://creativecommons.org/licenses/by-sa/4.0
SparkFun-Aesthetics: Released under the Creative Commons Attribution Share-Alike 4.0 License
SparkFun-Aesthetics: https://creativecommons.org/licenses/by-sa/4.0
